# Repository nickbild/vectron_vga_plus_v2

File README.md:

# Vectron VGA Plus v2

Vectron VGA Plus v2 generates a 640x480@60Hz VGA signal and has an interface that works with retro computers or microcontrollers.

## How It Works

Vectron VGA Plus v2 is an improvement on the [earlier design](https://github.com/nickbild/vectron_vga_plus).

The key to the simplified design of the Vectron VGA Plus boards is to use more RAM and less logic. So, for example, instead of having counters and flip flops, etc. to time each horizontal sync, that logic is embedded in the data in memory.  Memory addresses are sequentially incremented by an osciallator, and the contents of each memory address specify what signals to output (R/G/B/H sync/V sync).  Each of these memory addresses correspond with a specific pixel location (both visible and invisible) on the display.  When the end of a frame is reached, the address counters are reset, and the process starts all over to draw the next frame.

This second version offers a number of enhancements over the original:

- First, a second RAM chip was added to the design.  This allows for an active/standby scheme, such that the standby chip can receive updates without interupting the active chip that is displaying the video output.  When the host is done writing, the chips automatically switch roles in an instant, which updates the display without interruption.
<br><br>The original version used a single RAM chip, which led to momentary blips in the display during writes.  This new type of design would have been simpler to achieve by using dual-port RAM, but in the world of DIP chips suitable for retro projects, I couldn't source anything above about 4K, and I need a 256K chip for my selected resolution, so that wasn't a reasonable choice.

- The memory address at which the counter resets is no longer hard-wired.  It can now be tweaked by setting jumpers at the top of the board, which allows the signal to be fine-tuned, or even an entirely different resolution to be produced.  Since the storage of output signals in RAM offers total flexibility, it makes sense to allow for a frame of any number of pixels (up to the maximum allowed by RAM size).

- The size of the PCB was reduced significantly, and lots more capacitors were added to ensure perfect stability of signal under all conditions.  Additional power ports were also added to allow for grounding between additional peripherals.

To display graphics with the device, it first needs to be initialized with a blank screen (i.e. setting all the appropriate H syncs and V syncs), then pixels are written by setting the address pins to correspond with a pixel on screen, and the data pins to the RGB value, then issuing a simple latching signal.  The details are made clear in the [Arduino sketch](https://github.com/nickbild/vectron_vga_plus_v2/tree/main/vectron_vga_plus_v2_arduino_tester) that can be used to test the board out.  The tester will produce the following display output:

In the examples to follow, I have hooked Vectron VGA Plus v2 up to [Vectron VGA Plus Text Mode](https://github.com/nickbild/vectron_vga_plus_text_mode), which I use to simplify drawing characters to the screen.  The Text Mode module is in turn controlled by a breadboard prototype of the Vectron 65 Plus 6502 CPU-based computer (a PCB of this prototype will be created in the near future).

## Media

See it in action: [YouTube](https://www.youtube.com/watch?v=e3QL6s6VHpY)

Save time with a Hackaday comments generator, requiring only four lines of BASIC:

Here is the Vectron 65 Plus computer breadboard prototype (soon to be a PCB) interacting with the [Vectron VGA Plus Text Mode](https://github.com/nickbild/vectron_vga_plus_text_mode) board, which in turn uses the Vectron VGA Plus v2 board to display a VGA signal:

Vectron VGA Plus v2 circuit diagram:

## Bill of Materials

- 1 x 25.175 MHz crystal oscillator
- 2 x 74LS682
- 1 x 74AC32
- 1 x 74AC08
- 2 x AS6C4008-55PCN SRAM
- 2 x 74AC74
- 5 x 74AC161
- 2 x 74AC04
- 4 x 74AC244
- 10 x 74LS157
- 3 x 1000 uF electrolytic capactitors
- 30 x 0.01 uF ceramic capacitors
- 3 x 100 ohm resistors
- 3 x 200 ohm resistors
- 1 x VGA adapter
- 2.54" spaced male header pins
- 2.54" spaced jumpers
- PCB ([KiCad Design Files](https://github.com/nickbild/vectron_vga_plus_v2/tree/main/kicad))

## About the Author

[Nick A. Bild, MS](https://nickbild79.firebaseapp.com/#!/)

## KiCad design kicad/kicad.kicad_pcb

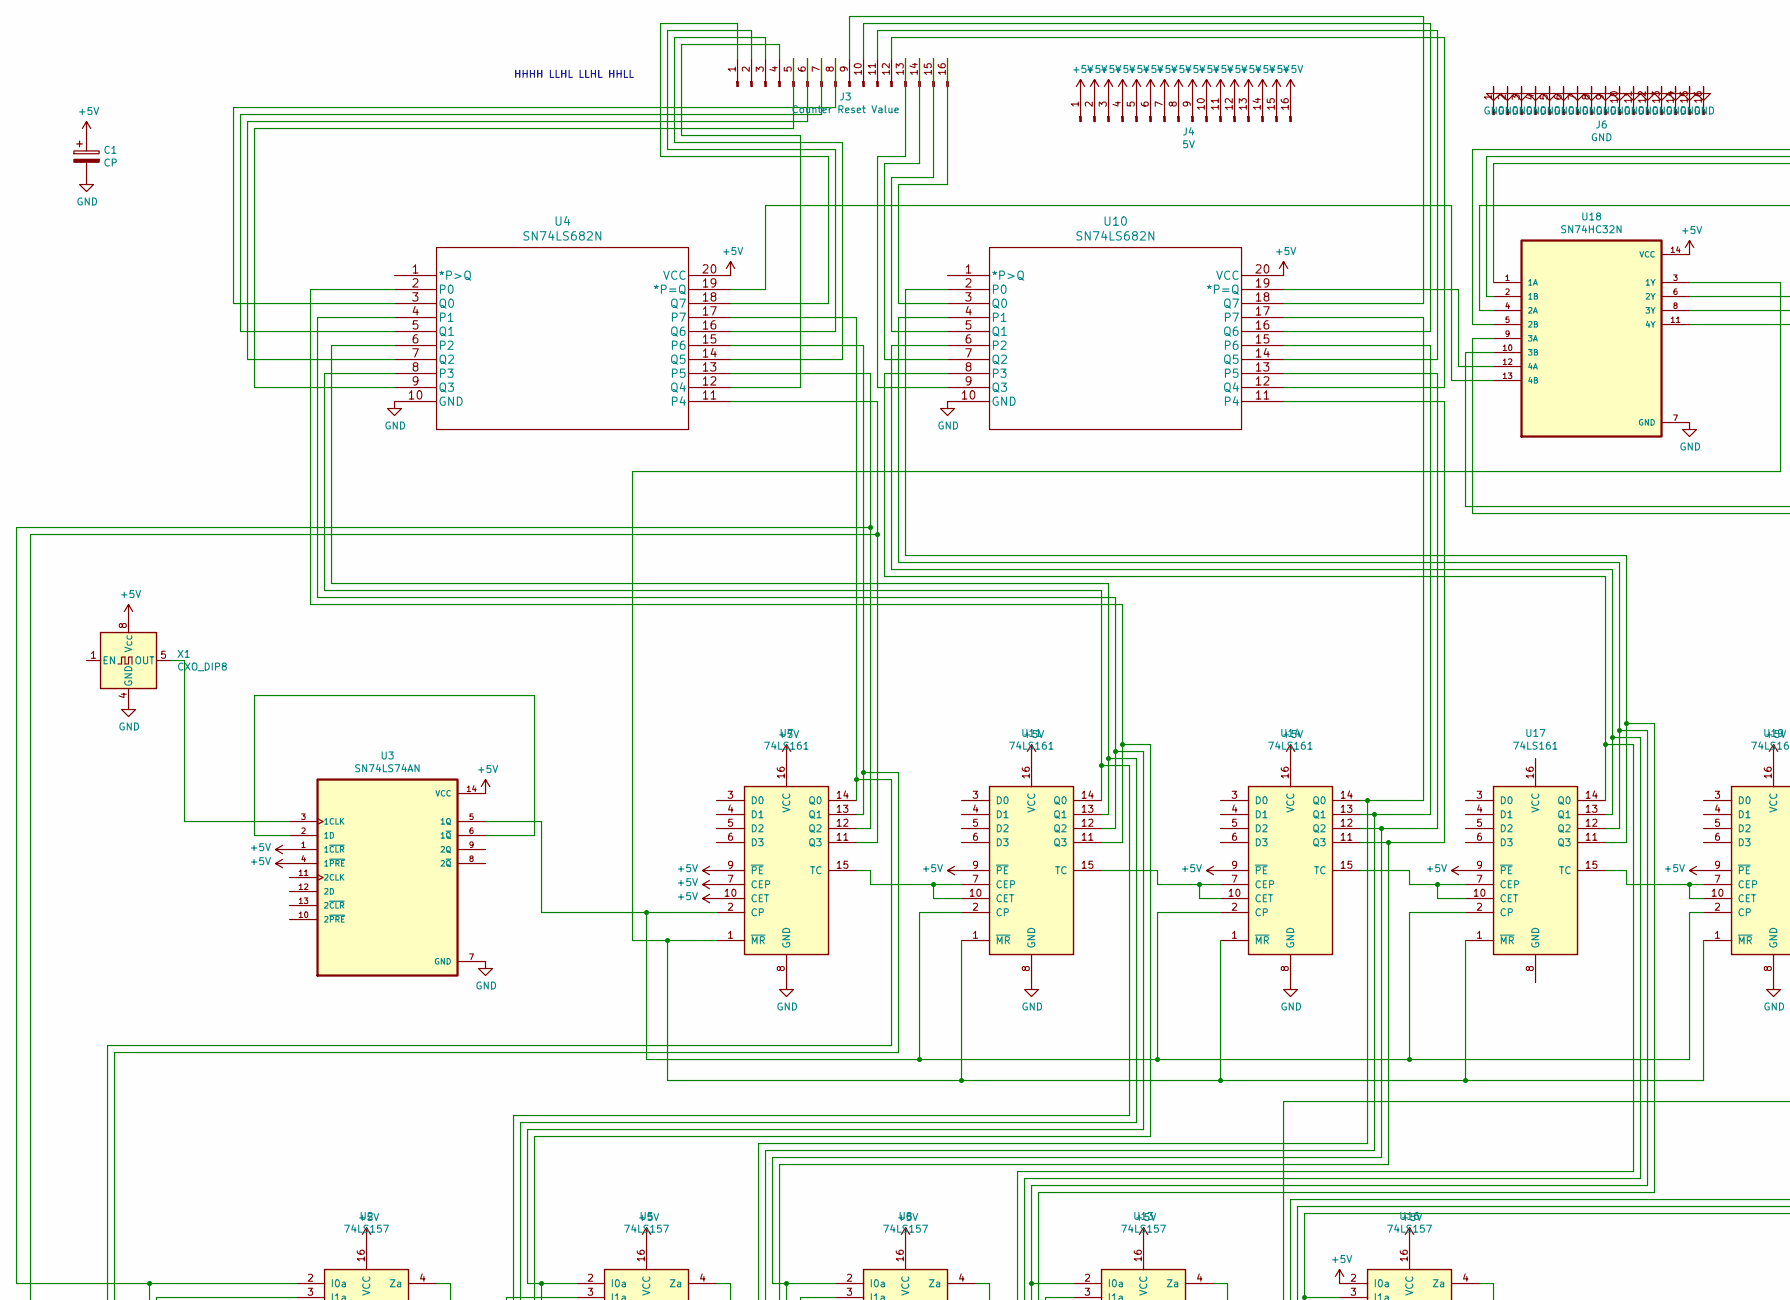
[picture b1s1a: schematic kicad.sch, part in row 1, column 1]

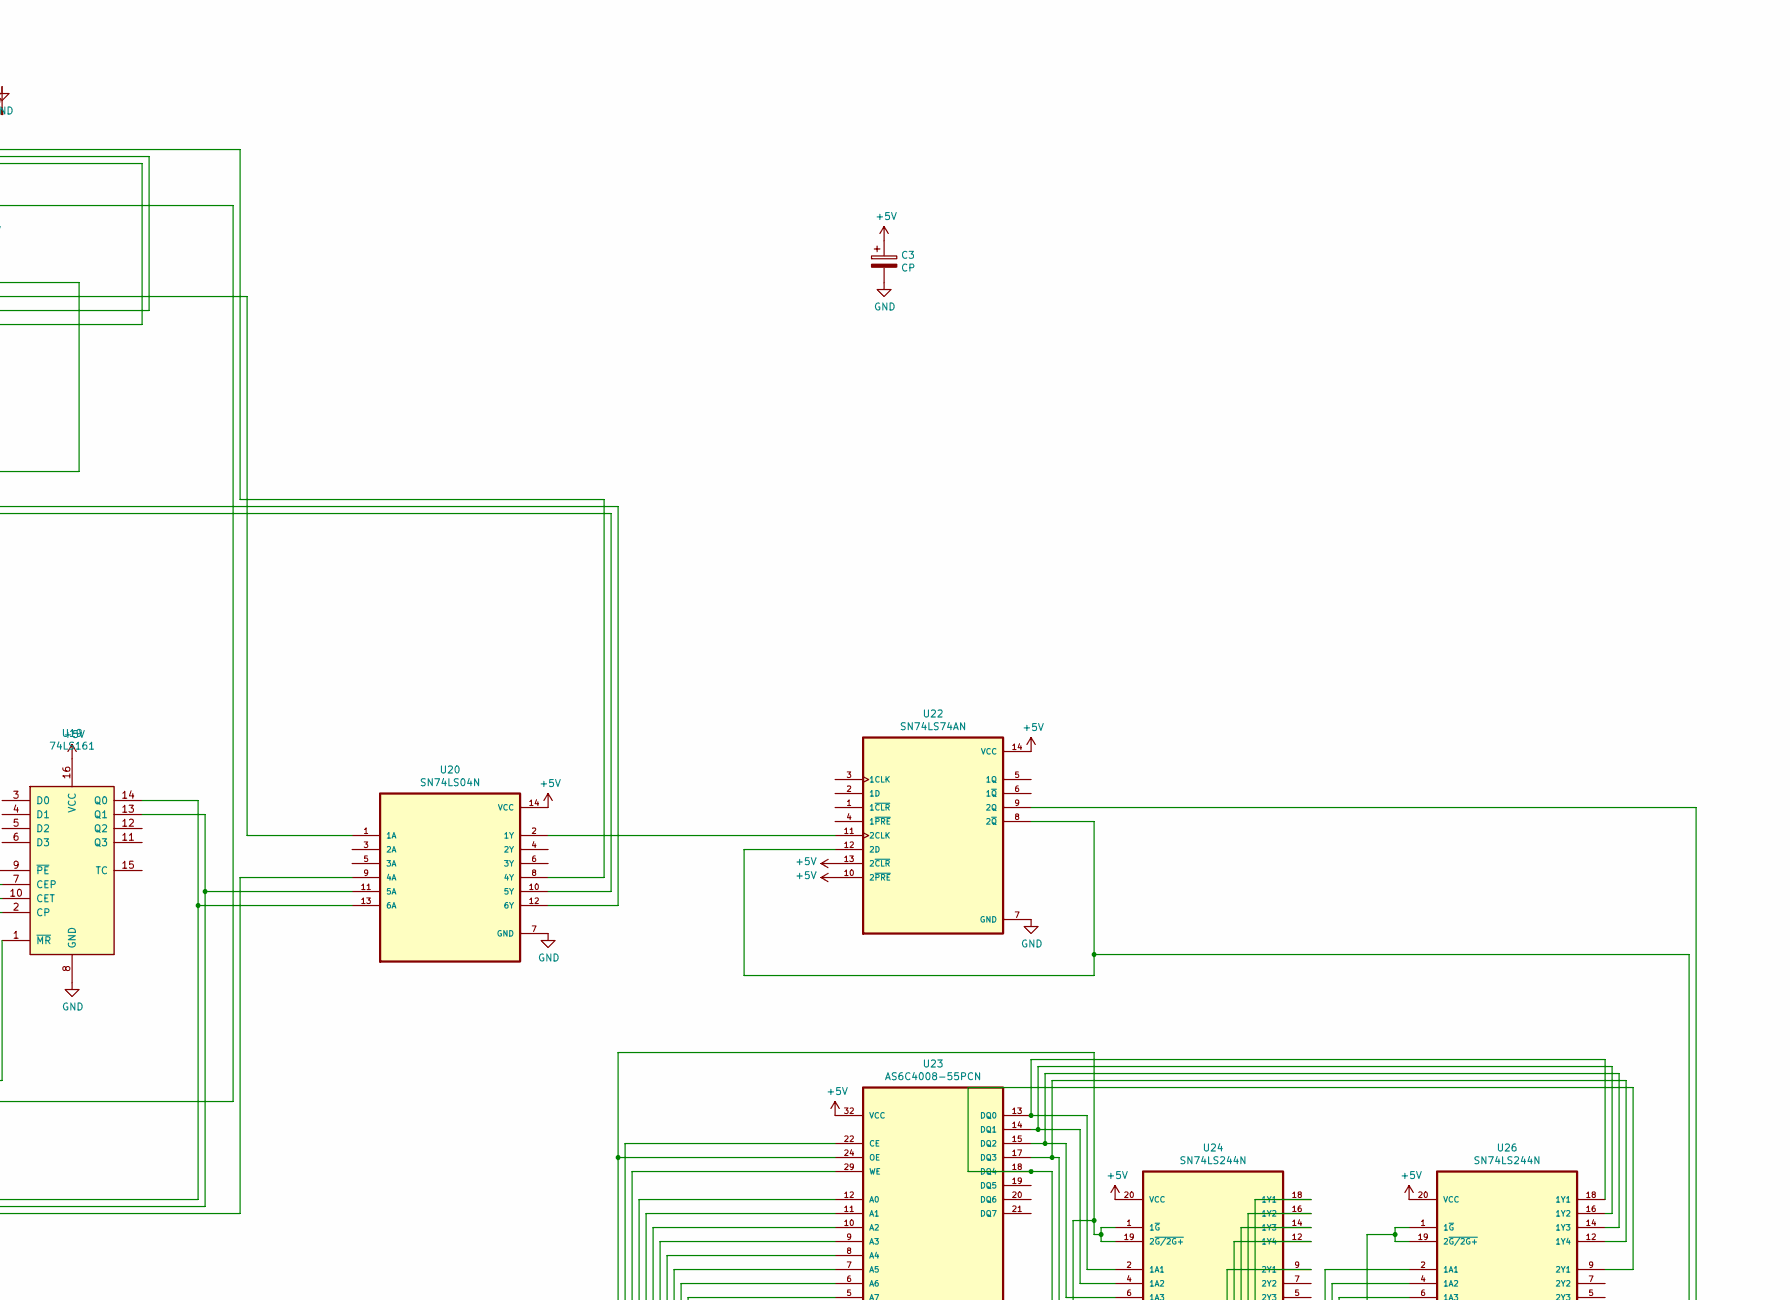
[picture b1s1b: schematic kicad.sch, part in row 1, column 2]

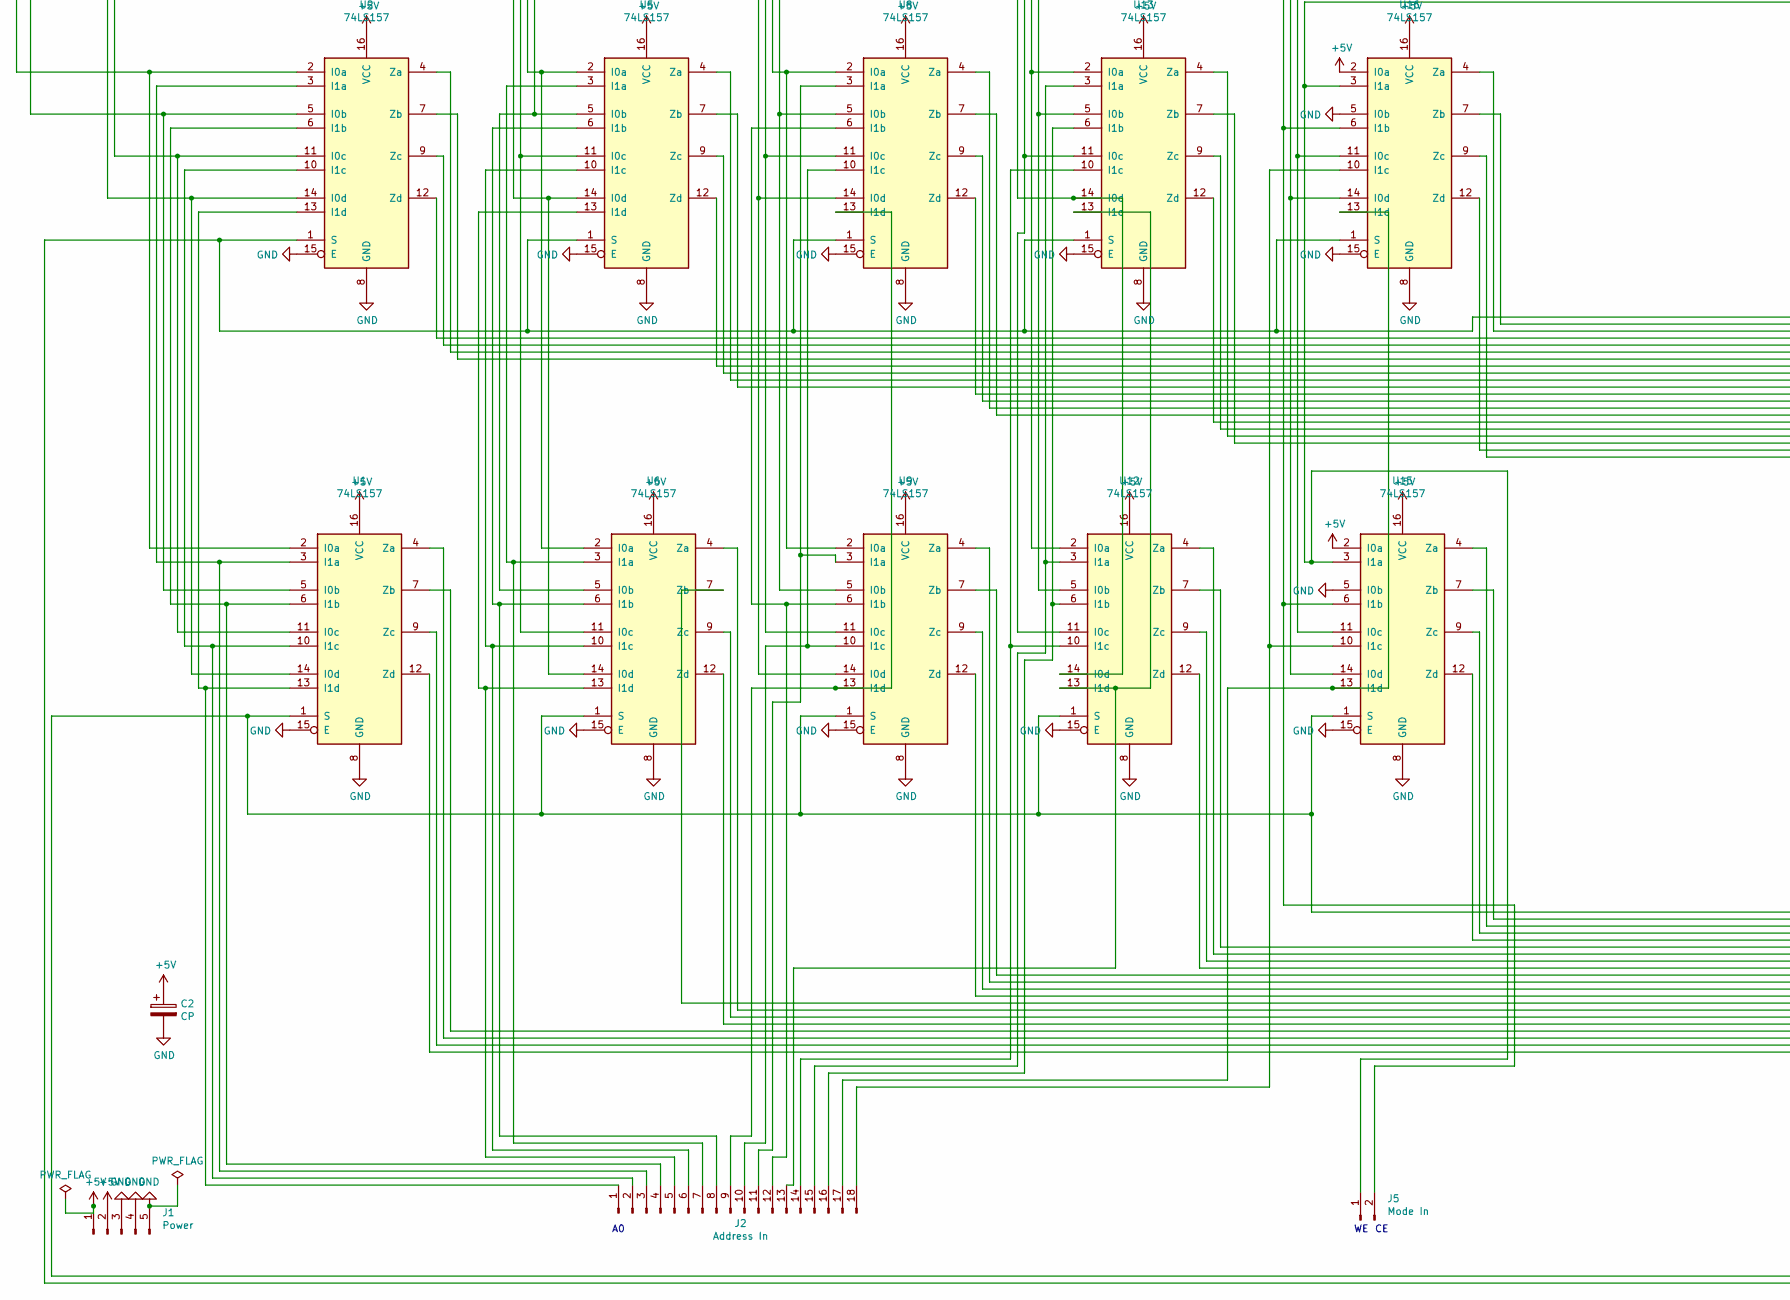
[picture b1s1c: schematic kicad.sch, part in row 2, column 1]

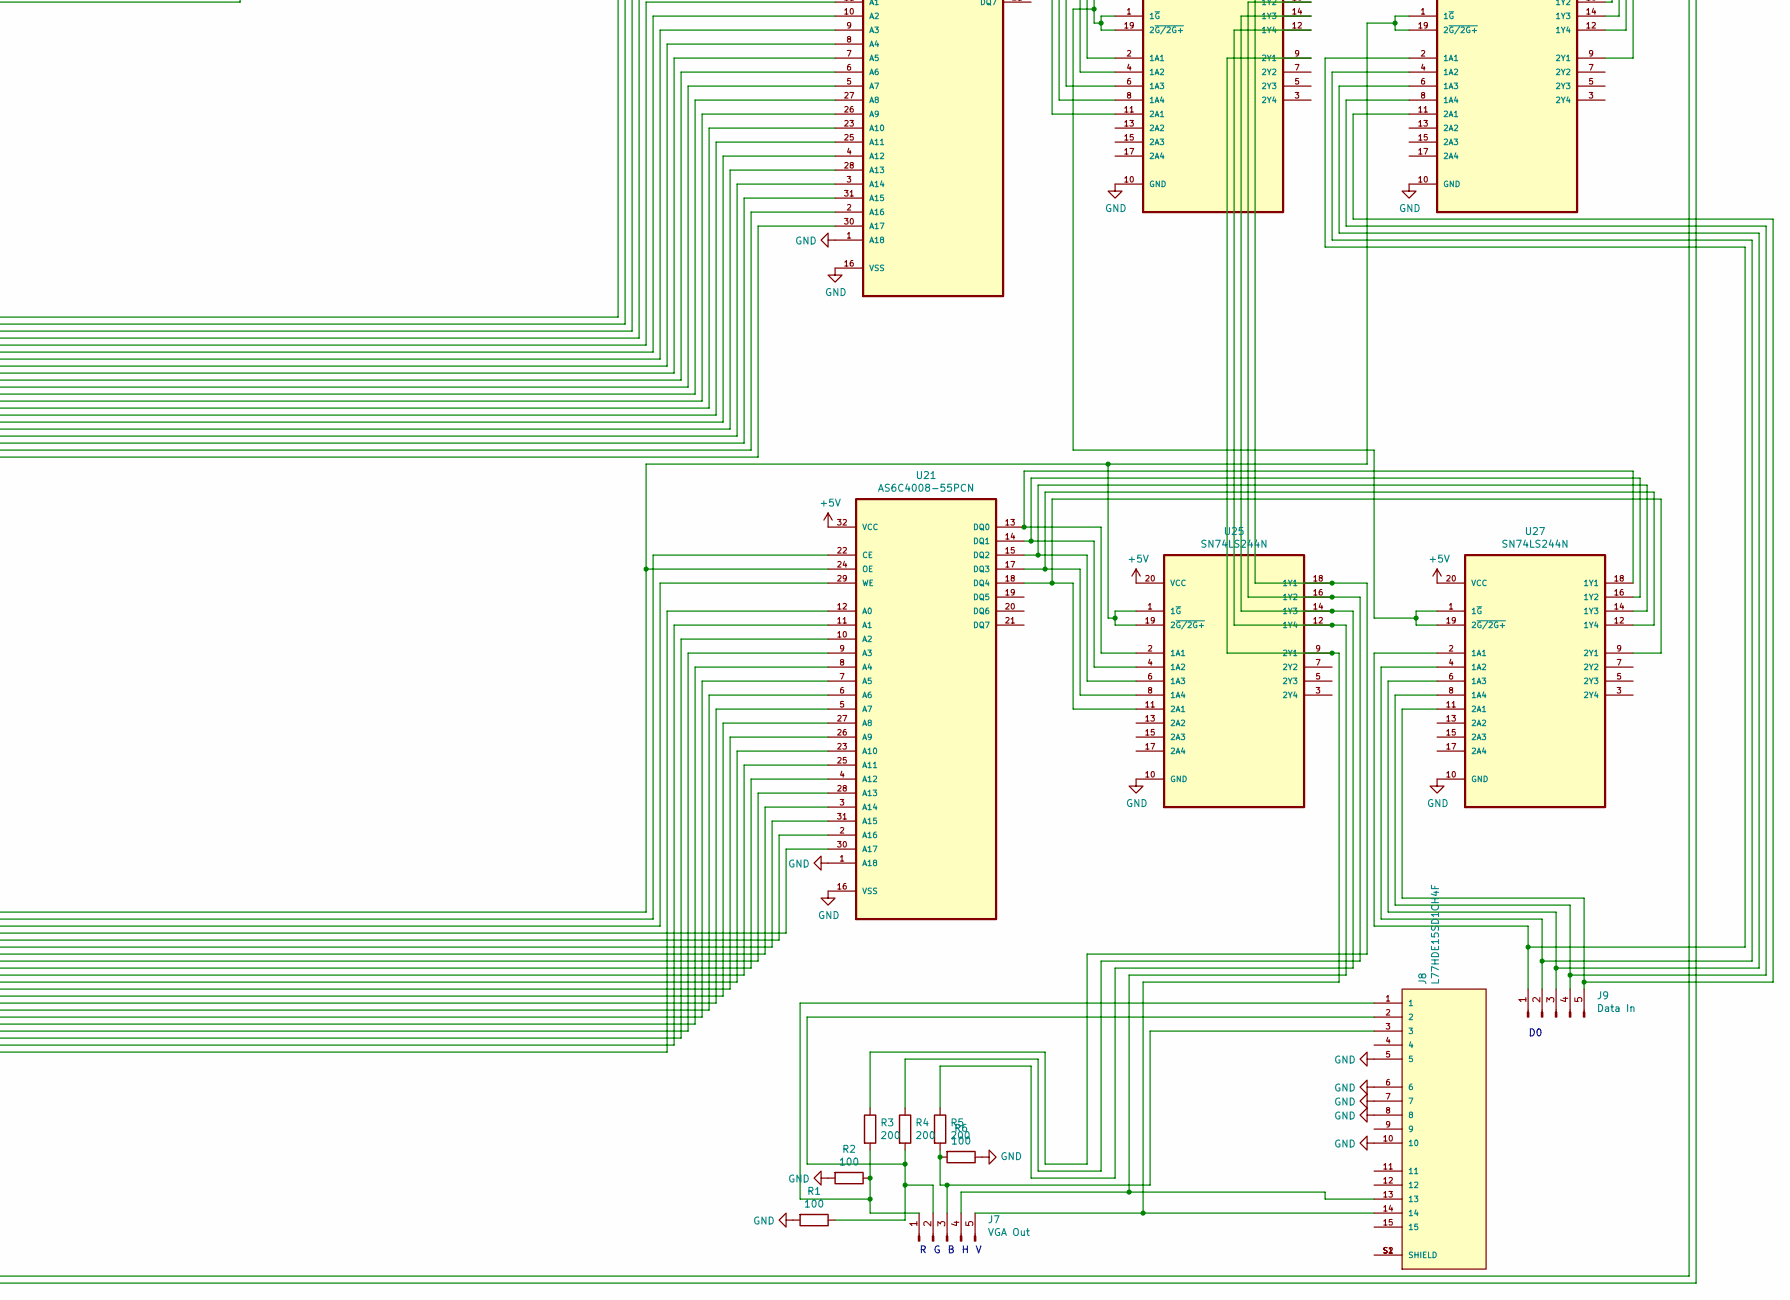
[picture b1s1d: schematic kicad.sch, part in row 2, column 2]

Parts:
C1, C2, C3: CP; CP_Radial_D10.0mm_P5.00mm
J1: Power; PinHeader_1x05_P2.54mm_Vertical
J2: Address In; PinHeader_1x18_P2.54mm_Vertical
J3: Counter Reset Value; PinHeader_1x16_P2.54mm_Vertical
J4: 5V; PinHeader_1x16_P2.54mm_Vertical
J5: Mode In; PinHeader_1x02_P2.54mm_Vertical
J6: GND; PinHeader_1x16_P2.54mm_Vertical
J7: VGA Out; PinHeader_1x05_P2.54mm_Vertical
J8: L77HDE15SD1CH4F; AMPHENOL_L77HDE15SD1CH4F; PARTREV N/A
J9: Data In; PinHeader_1x05_P2.54mm_Vertical
R1, R2, R6: 100; R_Axial_DIN0207_L6.3mm_D2.5mm_P7.62mm_Horizontal
R3, R4, R5: 200; R_Axial_DIN0207_L6.3mm_D2.5mm_P7.62mm_Horizontal
U1, U2, U5, U6, U8, U9, U12, U13, U15, U16: 74LS157; DIP-16_W7.62mm
U3, U22: SN74LS74AN; DIP-14_W7.62mm
U4, U10: SN74LS682N; DIP-20_W7.62mm
U7, U11, U14, U17, U19: 74LS161; DIP-16_W7.62mm
U18: SN74HC32N; DIP-14_W7.62mm
U20: SN74LS04N; DIP-14_W7.62mm
U21, U23: AS6C4008-55PCN; DIP-32_W15.24mm; MPN AS6C4008-55PCN
U24, U25, U26, U27: SN74LS244N; DIP-20_W7.62mm; MPN SN74LS244N
X1: CXO_DIP8; Oscillator_DIP-8

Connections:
+5V: C1.1, C2.1, C3.1, J1.1, J1.2, J4.1, J4.2, J4.3, J4.4, J4.5, J4.6, J4.7, J4.8, J4.9, J4.10, J4.11, J4.12, J4.13, J4.14, J4.15, J4.16, U1.16 (VCC), U2.16 (VCC), U3.1 (1~CLR), U3.4 (1~PRE), U3.14 (VCC), U4.20 (VCC), U5.16 (VCC), U6.16 (VCC), U7.7 (CEP), U7.9 (~PE), U7.10 (CET), U7.16 (VCC), U8.16 (VCC), U9.16 (VCC), U10.20 (VCC), U11.9 (~PE), U11.16 (VCC), U12.16 (VCC), U13.16 (VCC), U14.9 (~PE), U14.16 (VCC), U15.2 (I0a), U15.16 (VCC), U16.2 (I0a), U16.16 (VCC), U17.9 (~PE), U18.14 (VCC), U19.9 (~PE), U19.16 (VCC), U20.14 (VCC), U21.32 (VCC), U22.10 (2~PRE), U22.13 (2~CLR), U22.14 (VCC), U23.32 (VCC), U24.20 (VCC), U25.20 (VCC), U26.20 (VCC), U27.20 (VCC), X1.8 (Vcc)
GND: C1.2, C2.2, C3.2, J1.3, J1.4, J1.5, J6.1, J6.2, J6.3, J6.4, J6.5, J6.6, J6.7, J6.8, J6.9, J6.10, J6.11, J6.12, J6.13, J6.14, J6.15, J6.16, J8.5, J8.6, J8.7, J8.8, J8.10, R1.2, R2.2, R6.1, U1.8 (GND), U1.15 (E), U2.8 (GND), U2.15 (E), U3.7 (GND), U4.10 (GND), U5.8 (GND), U5.15 (E), U6.8 (GND), U6.15 (E), U7.8 (GND), U8.8 (GND), U8.15 (E), U9.8 (GND), U9.15 (E), U10.10 (GND), U11.8 (GND), U12.8 (GND), U12.15 (E), U13.8 (GND), U13.15 (E), U14.8 (GND), U15.5 (I0b), U15.8 (GND), U15.15 (E), U16.5 (I0b), U16.8 (GND), U16.15 (E), U18.7 (GND), U19.8 (GND), U20.7 (GND), U21.1 (A18), U21.16 (VSS), U22.7 (GND), U23.1 (A18), U23.16 (VSS), U24.10 (GND), U25.10 (GND), U26.10 (GND), U27.10 (GND), X1.4 (GND)
unnamed: J2.1, U1.13 (I1d), U2.13 (I1d)
unnamed: J2.2, U1.10 (I1c), U2.10 (I1c)
unnamed: J2.3, U1.3 (I1a), U2.3 (I1a)
unnamed: J2.4, U1.6 (I1b), U2.6 (I1b)
unnamed: J2.5, U5.13 (I1d), U6.13 (I1d)
unnamed: J2.6, U5.10 (I1c), U6.10 (I1c)
unnamed: J2.7, U5.3 (I1a), U6.3 (I1a)
unnamed: J2.8, U5.6 (I1b), U6.6 (I1b)
unnamed: J2.9, U8.13 (I1d), U9.13 (I1d)
unnamed: J2.10, U8.10 (I1c), U9.10 (I1c)
unnamed: J2.11, U8.3 (I1a), U9.3 (I1a)
unnamed: J2.12, U8.6 (I1b), U9.6 (I1b)
unnamed: J2.13, U12.13 (I1d), U13.13 (I1d)
unnamed: J2.14, U12.10 (I1c), U13.10 (I1c)
unnamed: J2.15, U12.3 (I1a), U13.3 (I1a)
unnamed: J2.16, U12.6 (I1b), U13.6 (I1b)
unnamed: J2.17, U15.13 (I1d), U16.13 (I1d)
unnamed: J2.18, U15.10 (I1c), U16.10 (I1c)
unnamed: J3.1, U4.18 (Q7)
unnamed: J3.2, U4.16 (Q6)
unnamed: J3.3, U4.14 (Q5)
unnamed: J3.4, U4.12 (Q4)
unnamed: J3.5, U4.9 (Q3)
unnamed: J3.6, U4.7 (Q2)
unnamed: J3.7, U4.5 (Q1)
unnamed: J3.8, U4.3 (Q0)
unnamed: J3.9, U10.18 (Q7)
unnamed: J3.10, U10.16 (Q6)
unnamed: J3.11, U10.14 (Q5)
unnamed: J3.12, U10.12 (Q4)
unnamed: J3.13, U10.9 (Q3)
unnamed: J3.14, U10.7 (Q2)
unnamed: J3.15, U10.5 (Q1)
unnamed: J3.16, U10.3 (Q0)
unnamed: J5.1, U15.3 (I1a), U16.3 (I1a), U20.9 (4A)
unnamed: J5.2, U15.6 (I1b), U16.6 (I1b), U18.4 (2A)
unnamed: J7.1, J8.1, R2.1, R3.2
unnamed: J7.2, J8.2, R1.1, R4.2
unnamed: J7.3, J8.3, R5.2, R6.2
unnamed: J7.4, J8.13, U24.12 (1Y4), U25.12 (1Y4)
unnamed: J7.5, J8.14, U24.9 (2Y1), U25.9 (2Y1)
unnamed: J8.S1 (SHIELD), J8.S2 (SHIELD)
unnamed: J9.1, U26.2 (1A1), U27.2 (1A1)
unnamed: J9.2, U26.4 (1A2), U27.4 (1A2)
unnamed: J9.3, U26.6 (1A3), U27.6 (1A3)
unnamed: J9.4, U26.8 (1A4), U27.8 (1A4)
unnamed: J9.5, U26.11 (2A1), U27.11 (2A1)
unnamed: R3.1, U24.18 (1Y1), U25.18 (1Y1)
unnamed: R4.1, U24.16 (1Y2), U25.16 (1Y2)
unnamed: R5.1, U24.14 (1Y3), U25.14 (1Y3)
unnamed: U1.1 (S), U6.1 (S), U9.1 (S), U12.1 (S), U15.1 (S), U21.24 (OE), U22.8 (2~Q), U22.12 (2D), U25.1 (1~G), U25.19 (2~G/2G+), U26.1 (1~G), U26.19 (2~G/2G+)
unnamed: U1.2 (I0a), U2.2 (I0a), U4.13 (P5), U7.12 (Q2)
unnamed: U1.4 (Za), U21.10 (A2)
unnamed: U1.5 (I0b), U2.5 (I0b), U4.11 (P4), U7.11 (Q3)
unnamed: U1.7 (Zb), U21.9 (A3)
unnamed: U1.9 (Zc), U21.11 (A1)
unnamed: U1.11 (I0c), U2.11 (I0c), U4.15 (P6), U7.13 (Q1)
unnamed: U1.12 (Zd), U21.12 (A0)
unnamed: U1.14 (I0d), U2.14 (I0d), U4.17 (P7), U7.14 (Q0)
unnamed: U2.4 (Za), U23.10 (A2)
unnamed: U2.7 (Zb), U23.9 (A3)
unnamed: U2.9 (Zc), U23.11 (A1)
unnamed: U2.12 (Zd), U23.12 (A0)
unnamed: U3.2 (1D), U3.6 (1~Q)
unnamed: U3.3 (1CLK), X1.5 (OUT)
unnamed: U10.2 (P0), U12.5 (I0b), U13.5 (I0b), U17.11 (Q3)
unnamed: U10.4 (P1), U12.2 (I0a), U13.2 (I0a), U17.12 (Q2)
unnamed: U10.6 (P2), U12.11 (I0c), U13.11 (I0c), U17.13 (Q1)
unnamed: U10.8 (P3), U12.14 (I0d), U13.14 (I0d), U17.14 (Q0)
unnamed: U8.5 (I0b), U9.5 (I0b), U10.11 (P4), U14.11 (Q3)
unnamed: U8.2 (I0a), U9.2 (I0a), U10.13 (P5), U14.12 (Q2)
unnamed: U8.11 (I0c), U9.11 (I0c), U10.15 (P6), U14.13 (Q1)
unnamed: U8.14 (I0d), U9.14 (I0d), U10.17 (P7), U14.14 (Q0)
unnamed: U10.19 (*P=Q), U18.12 (4A)
unnamed: U7.1 (~MR), U11.1 (~MR), U14.1 (~MR), U17.1 (~MR), U18.3 (1Y), U19.1 (~MR)
unnamed: U3.5 (1Q), U7.2 (CP), U11.2 (CP), U14.2 (CP), U17.2 (CP), U19.2 (CP)
unnamed: U7.15 (TC), U11.7 (CEP), U11.10 (CET)
unnamed: U4.2 (P0), U5.5 (I0b), U6.5 (I0b), U11.11 (Q3)
unnamed: U4.4 (P1), U5.2 (I0a), U6.2 (I0a), U11.12 (Q2)
unnamed: U4.6 (P2), U5.11 (I0c), U6.11 (I0c), U11.13 (Q1)
unnamed: U4.8 (P3), U5.14 (I0d), U6.14 (I0d), U11.14 (Q0)
unnamed: U11.15 (TC), U14.7 (CEP), U14.10 (CET)
unnamed: U12.4 (Za), U21.3 (A14)
unnamed: U12.7 (Zb), U21.31 (A15)
unnamed: U12.9 (Zc), U21.28 (A13)
unnamed: U12.12 (Zd), U21.4 (A12)
unnamed: U2.1 (S), U5.1 (S), U8.1 (S), U13.1 (S), U16.1 (S), U22.9 (2Q), U23.24 (OE), U24.1 (1~G), U24.19 (2~G/2G+), U27.1 (1~G), U27.19 (2~G/2G+)
unnamed: U13.4 (Za), U23.3 (A14)
unnamed: U13.7 (Zb), U23.31 (A15)
unnamed: U13.9 (Zc), U23.28 (A13)
unnamed: U13.12 (Zd), U23.4 (A12)
unnamed: U14.15 (TC), U17.7 (CEP), U17.10 (CET)
unnamed: U15.4 (Za), U21.29 (WE)
unnamed: U15.7 (Zb), U21.22 (CE)
unnamed: U15.9 (Zc), U21.30 (A17)
unnamed: U15.11 (I0c), U16.11 (I0c), U19.13 (Q1), U20.11 (5A)
unnamed: U15.12 (Zd), U21.2 (A16)
unnamed: U15.14 (I0d), U16.14 (I0d), U19.14 (Q0), U20.13 (6A)
unnamed: U16.4 (Za), U23.29 (WE)
unnamed: U16.7 (Zb), U23.22 (CE)
unnamed: U16.9 (Zc), U23.30 (A17)
unnamed: U16.12 (Zd), U23.2 (A16)
unnamed: U17.15 (TC), U19.7 (CEP), U19.10 (CET)
unnamed: U18.1 (1A), U18.11 (4Y)
unnamed: U18.2 (1B), U18.8 (3Y)
unnamed: U18.5 (2B), U20.8 (4Y)
unnamed: U18.6 (2Y), U20.1 (1A)
unnamed: U18.9 (3A), U20.10 (5Y)
unnamed: U18.10 (3B), U20.12 (6Y)
unnamed: U4.19 (*P=Q), U18.13 (4B)
unnamed: U20.2 (1Y), U22.11 (2CLK)
unnamed: U6.7 (Zb), U21.5 (A7)
unnamed: U6.4 (Za), U21.6 (A6)
unnamed: U6.9 (Zc), U21.7 (A5)
unnamed: U6.12 (Zd), U21.8 (A4)
unnamed: U21.13 (DQ0), U25.2 (1A1), U27.18 (1Y1)
unnamed: U21.14 (DQ1), U25.4 (1A2), U27.16 (1Y2)
unnamed: U21.15 (DQ2), U25.6 (1A3), U27.14 (1Y3)
unnamed: U21.17 (DQ3), U25.8 (1A4), U27.12 (1Y4)
unnamed: U21.18 (DQ4), U25.11 (2A1), U27.9 (2Y1)
unnamed: U9.4 (Za), U21.23 (A10)
unnamed: U9.7 (Zb), U21.25 (A11)
unnamed: U9.9 (Zc), U21.26 (A9)
unnamed: U9.12 (Zd), U21.27 (A8)
unnamed: U5.7 (Zb), U23.5 (A7)
unnamed: U5.4 (Za), U23.6 (A6)
unnamed: U5.9 (Zc), U23.7 (A5)
unnamed: U5.12 (Zd), U23.8 (A4)
unnamed: U23.13 (DQ0), U24.2 (1A1), U26.18 (1Y1)
unnamed: U23.14 (DQ1), U24.4 (1A2), U26.16 (1Y2)
unnamed: U23.15 (DQ2), U24.6 (1A3), U26.14 (1Y3)
unnamed: U23.17 (DQ3), U24.8 (1A4), U26.12 (1Y4)
unnamed: U23.18 (DQ4), U24.11 (2A1), U26.9 (2Y1)
unnamed: U8.4 (Za), U23.23 (A10)
unnamed: U8.7 (Zb), U23.25 (A11)
unnamed: U8.9 (Zc), U23.26 (A9)
unnamed: U8.12 (Zd), U23.27 (A8)

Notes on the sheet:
HHHH LLHL LLHL HHLL

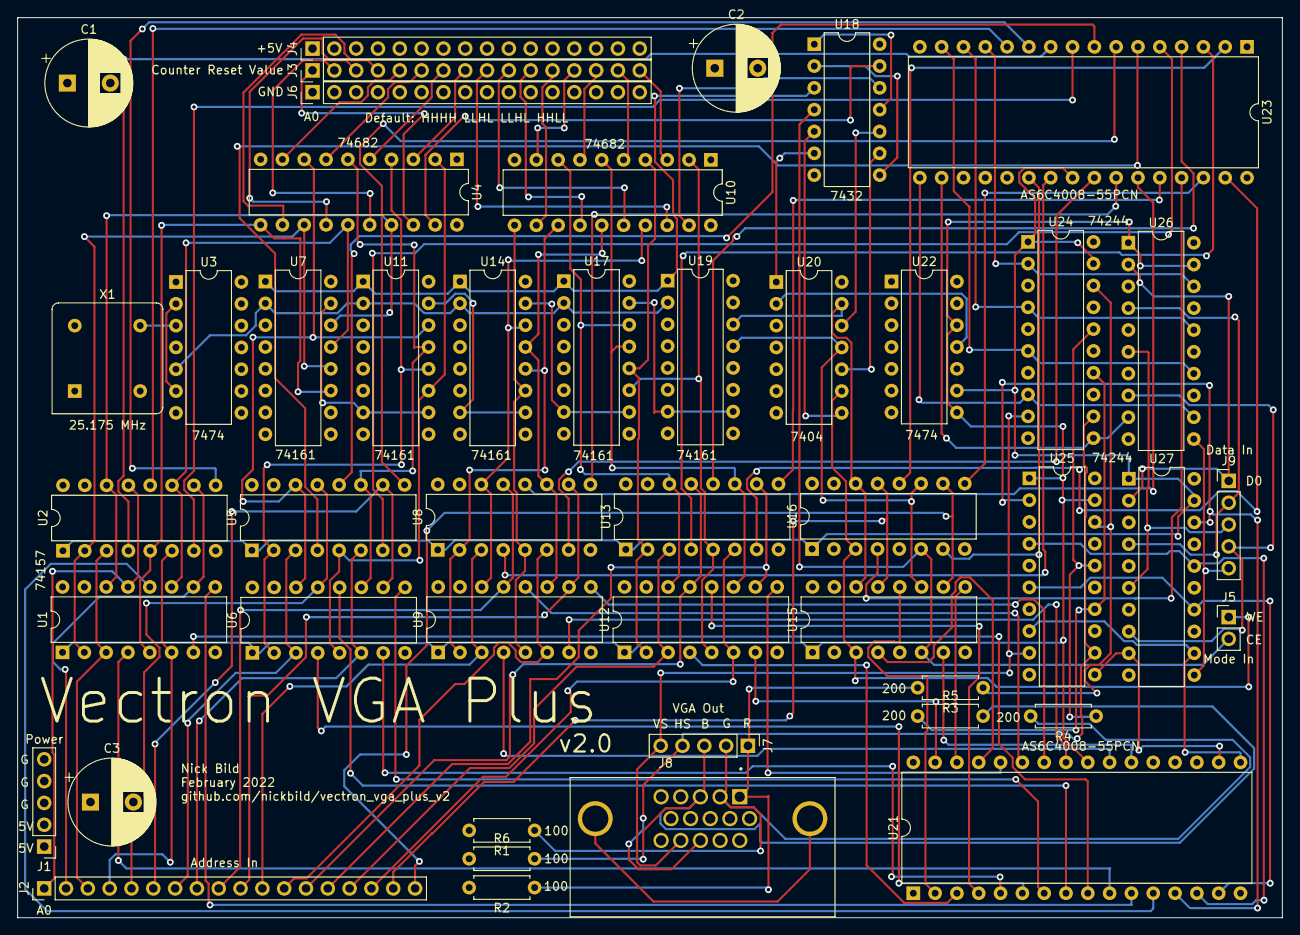
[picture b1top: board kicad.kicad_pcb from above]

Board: 4 copper layers, 147.3 x 104.8 mm, 46 parts (0 on the bottom side), 139 nets.

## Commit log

2022-02-06 Initial commit.
2022-02-06 Save progress on schematic.
2022-02-07 Save progress on PCB.
2022-02-25 Fix unconnected power lines.
2022-04-02 Test chip swapping.
2022-04-02 Update schematic to account for SRAM enable time.
2022-04-03 Update PCB to account for SRAM enable time.
2022-04-03 Add caps and addl. power to schematic.
2022-04-03 Add caps and addl. power to PCB.
2022-04-25 Update documentation.
